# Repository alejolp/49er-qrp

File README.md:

NorCal 49er QRP Eagle PCB
==============

This is the PCB design the NorCal's 49er QRP 40M CW transceiver. The original design can be found here:

  http://www.norcalqrp.org/files/49erOrigMnl.pdf
  
Some modificatins to this design can be found here:

  http://www.amqrp.org/kits/49er/49mod.html

  - Designed by Wayne Burdick, N6KR
  - Manual by Doug Hendricks, KI6DS
  - PCB by Alejandro Santos, LU4EXT, alejolp@gmail.com

Pictures
========

The PCB design files can be found as PNG files, here:

  - https://github.com/alejolp/49er-qrp/raw/master/pcb1.png
  - https://github.com/alejolp/49er-qrp/raw/master/pcb2.png
  - https://github.com/alejolp/49er-qrp/raw/master/pcb3.png
  - https://github.com/alejolp/49er-qrp/raw/master/sch1.png

For some construction pictures you can visit my Flickr set:

  - http://www.flickr.com/photos/alejolp/sets/72157638988100786

License
=======

This work is licensed under the Creative Commons Attribution-ShareAlike 3.0 Unported License. To view a copy of this license, visit http://creativecommons.org/licenses/by-sa/3.0/ or send a letter to Creative Commons, 444 Castro Street, Suite 900, Mountain View, California, 94041, USA.

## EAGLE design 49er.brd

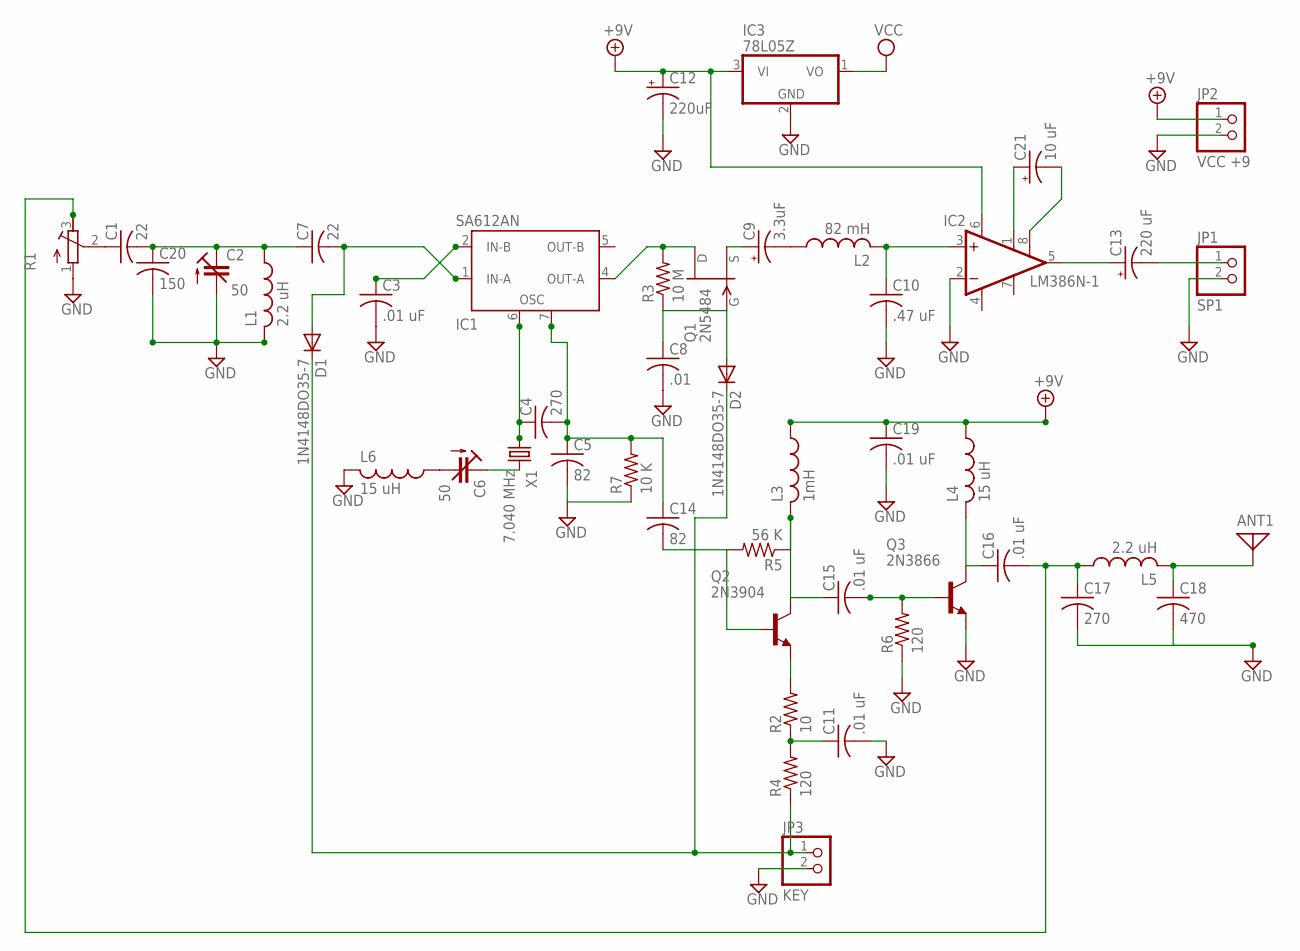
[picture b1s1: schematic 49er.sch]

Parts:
ANT1: ANTENNA; PAD-01
C1, C7: 22; C025-025X050
C2, C6: 50; CTRIM3008
C3, C11, C15, C16, C19: .01 uF; C025-025X050
C4, C17: 270; C025-025X050
C5, C14: 82; C025-025X050
C8: .01; C025-025X050
C9: 3.3uF; E2,5-7
C10: .47 uF; C025-025X050
C12: 220uF; E2,5-7
C13: 220 uF; E2,5-7
C18: 470; C025-025X050
C20: 150; C025-025X050
C21: 10 uF; E2,5-7
D1, D2: 1N4148DO35-7; DO35-7
IC1: SA612AN; DIL08
IC2: LM386N-1; DIL08
IC3: 78L05Z; TO92
JP1: SP1; 1X02
JP2: VCC +9; 1X02
JP3: KEY; 1X02
L1, L5: 2.2 uH; 0207/10
L2: 82 mH; TJ4-U1
L3: 1mH; 0207/10
L4, L6: 15 uH; 0207/10
Q1: 2N5484; TO92-
Q2: 2N3904; TO92
Q3: 2N3866; TO92
R1: R-TRIMM3296W; RTRIM3296W
R2: 10; 0207/10
R3: 10 M; 0207/10
R4, R6: 120; 0207/10
R5: 56 K; 0207/10
R7: 10 K; 0207/10
X1: 7.040 MHz; HC49/S

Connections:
+9V: C12.+, C19.1, IC2.6 (VS), IC3.3 (VI), JP2.1, L3.1, L4.1
GND: C2.- (A), C3.2, C5.2, C8.2, C10.2, C11.2, C12.-, C17.2, C18.2, C19.2, C20.2, IC1.3 (GND), IC2.2 (-IN), IC2.4 (GND), IC3.2 (GND), JP1.2, JP2.2, JP3.2, L1.2, L6.2, Q3.1 (E), R1.1 (E), R6.1, R7.1
unnamed: D1.C, D2.C, JP3.1, R4.1
unnamed: C1.1, R1.2 (S)
unnamed: C1.2, C2.+ (E), C7.1, C20.1, L1.1
unnamed: C3.1, IC1.2 (IN-B)
unnamed: C4.2, C5.1, C14.1, IC1.7 (OSC'), R7.2
unnamed: C7.2, D1.A, IC1.1 (IN-A)
unnamed: C6.+ (E), X1.2
unnamed: C4.1, IC1.6 (OSC), X1.1
unnamed: C9.-, L2.1
unnamed: C6.- (A), L6.1
unnamed: IC1.4 (OUT-A), Q1.3 (D), R3.2
unnamed: C9.+, Q1.2 (S)
unnamed: C8.1, D2.A, Q1.1 (G), R3.1
unnamed: C10.1, IC2.3 (+IN), L2.2
unnamed: C13.-, JP1.1
unnamed: C13.+, IC2.5 (OUT)
unnamed: C21.+, IC2.1 (GAIN)
unnamed: C21.-, IC2.8 (GAIN)
unnamed: C16.1, L4.2, Q3.3 (C)
unnamed: C16.2, C17.1, L5.1, R1.3 (A)
unnamed: ANT1.1, C18.1, L5.2
unnamed: C14.2, Q2.2 (B), R5.2
unnamed: C15.2, Q3.2 (B), R6.2
unnamed: C15.1, L3.2, Q2.1 (C), R5.1
unnamed: Q2.3 (E), R2.2
unnamed: C11.1, R2.1, R4.2
VCC: IC1.8 (VCC), IC3.1 (VO)

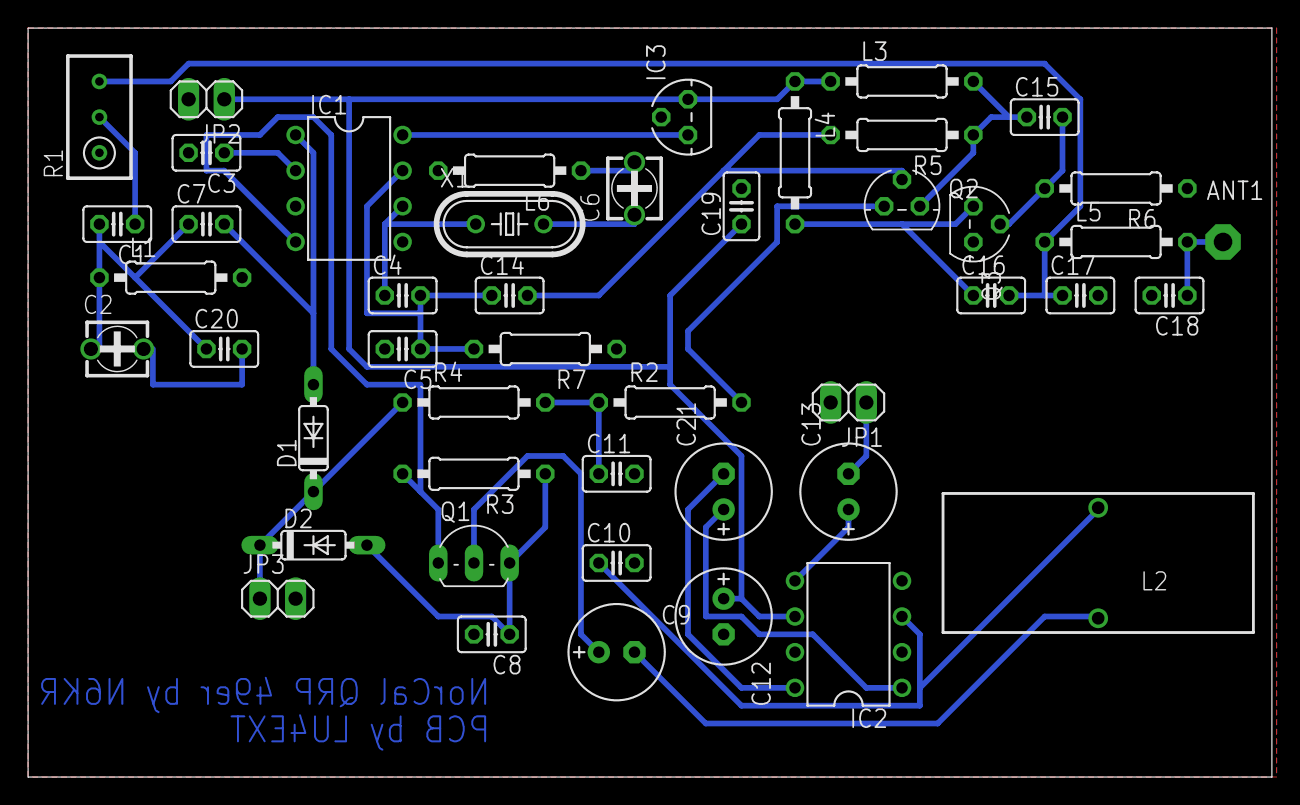
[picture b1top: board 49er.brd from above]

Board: 2 copper layers, 88.6 x 53.3 mm, 47 parts (0 on the bottom side), 29 nets.

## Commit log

2013-12-24 initial
2013-12-24 imagenes
2013-12-24 cambios menores
2013-12-24 readme
2013-12-31 GND bug fix
